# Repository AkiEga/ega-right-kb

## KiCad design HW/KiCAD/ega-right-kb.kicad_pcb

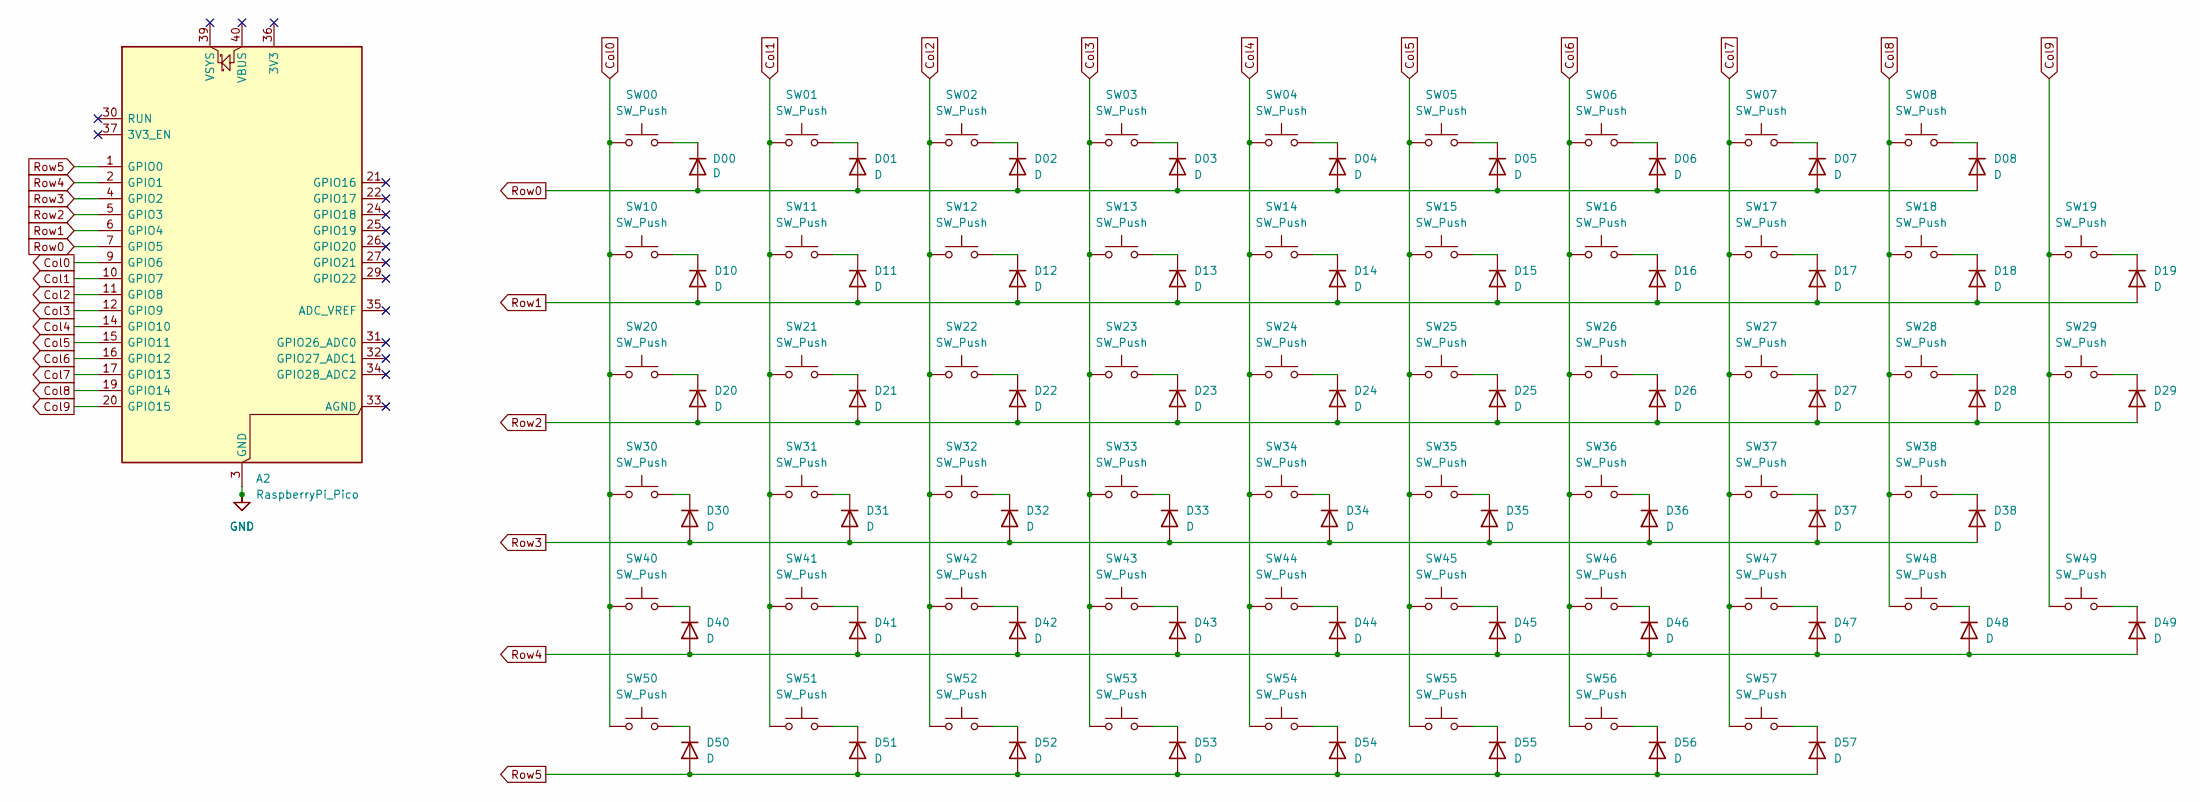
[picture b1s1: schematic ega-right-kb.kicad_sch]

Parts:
A2: RaspberryPi_Pico; RaspberryPi_Pico_Common_THT
D00, D01, D02, D03, D04, D05, D06, D07, D08, D10, D11, D12, D13, D14, D15, D16, D17, D18, D19, D20, D21, D22, D23, D24, D25, D26, D27, D28, D29, D30, D31, D32, D33, D34, D35, D36, D37, D38, D40, D41, D42, D43, D44, D45, D46, D47, D48, D49, D50, D51, D52, D53, D54, D55, D56, D57: D; D_SOD-123
SW00, SW01, SW02, SW03, SW04, SW05, SW06, SW07, SW08, SW10, SW11, SW12, SW13, SW14, SW15, SW16, SW17, SW18, SW19, SW20, SW21, SW22, SW23, SW24, SW25, SW26, SW27, SW28, SW29, SW30, SW31, SW32, SW33, SW34, SW35, SW36, SW37, SW38, SW40, SW41, SW42, SW43, SW44, SW45, SW46, SW47, SW48, SW49, SW50, SW51, SW52, SW53, SW54, SW55, SW56, SW57: SW_Push; SW_Hotswap_Kailh_MX_1.00u

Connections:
Col0: A2.9 (GPIO6), SW00.1, SW10.1, SW20.1, SW30.1, SW40.1, SW50.1
Col1: A2.10 (GPIO7), SW01.1, SW11.1, SW21.1, SW31.1, SW41.1, SW51.1
Col2: A2.11 (GPIO8), SW02.1, SW12.1, SW22.1, SW32.1, SW42.1, SW52.1
Col3: A2.12 (GPIO9), SW03.1, SW13.1, SW23.1, SW33.1, SW43.1, SW53.1
Col4: A2.14 (GPIO10), SW04.1, SW14.1, SW24.1, SW34.1, SW44.1, SW54.1
Col5: A2.15 (GPIO11), SW05.1, SW15.1, SW25.1, SW35.1, SW45.1, SW55.1
Col6: A2.16 (GPIO12), SW06.1, SW16.1, SW26.1, SW36.1, SW46.1, SW56.1
Col7: A2.17 (GPIO13), SW07.1, SW17.1, SW27.1, SW37.1, SW47.1, SW57.1
Col8: A2.19 (GPIO14), SW08.1, SW18.1, SW28.1, SW38.1, SW48.1
Col9: A2.20 (GPIO15), SW19.1, SW29.1, SW49.1
GND: A2.3 (GND), A2.8 (GND), A2.13 (GND), A2.18 (GND), A2.23 (GND), A2.28 (GND), A2.38 (GND)
unnamed: D00.1 (K), SW00.2
unnamed: D01.1 (K), SW01.2
unnamed: D02.1 (K), SW02.2
unnamed: D03.1 (K), SW03.2
unnamed: D04.1 (K), SW04.2
unnamed: D05.1 (K), SW05.2
unnamed: D06.1 (K), SW06.2
unnamed: D07.1 (K), SW07.2
unnamed: D08.1 (K), SW08.2
unnamed: D10.1 (K), SW10.2
unnamed: D11.1 (K), SW11.2
unnamed: D12.1 (K), SW12.2
unnamed: D13.1 (K), SW13.2
unnamed: D14.1 (K), SW14.2
unnamed: D15.1 (K), SW15.2
unnamed: D16.1 (K), SW16.2
unnamed: D17.1 (K), SW17.2
unnamed: D18.1 (K), SW18.2
unnamed: D19.1 (K), SW19.2
unnamed: D20.1 (K), SW20.2
unnamed: D21.1 (K), SW21.2
unnamed: D22.1 (K), SW22.2
unnamed: D23.1 (K), SW23.2
unnamed: D24.1 (K), SW24.2
unnamed: D25.1 (K), SW25.2
unnamed: D26.1 (K), SW26.2
unnamed: D27.1 (K), SW27.2
unnamed: D28.1 (K), SW28.2
unnamed: D29.1 (K), SW29.2
unnamed: D30.1 (K), SW30.2
unnamed: D31.1 (K), SW31.2
unnamed: D32.1 (K), SW32.2
unnamed: D33.1 (K), SW33.2
unnamed: D34.1 (K), SW34.2
unnamed: D35.1 (K), SW35.2
unnamed: D36.1 (K), SW36.2
unnamed: D37.1 (K), SW37.2
unnamed: D38.1 (K), SW38.2
unnamed: D40.1 (K), SW40.2
unnamed: D41.1 (K), SW41.2
unnamed: D42.1 (K), SW42.2
unnamed: D43.1 (K), SW43.2
unnamed: D44.1 (K), SW44.2
unnamed: D45.1 (K), SW45.2
unnamed: D46.1 (K), SW46.2
unnamed: D47.1 (K), SW47.2
unnamed: D48.1 (K), SW48.2
unnamed: D49.1 (K), SW49.2
unnamed: D50.1 (K), SW50.2
unnamed: D51.1 (K), SW51.2
unnamed: D52.1 (K), SW52.2
unnamed: D53.1 (K), SW53.2
unnamed: D54.1 (K), SW54.2
unnamed: D55.1 (K), SW55.2
unnamed: D56.1 (K), SW56.2
unnamed: D57.1 (K), SW57.2
Row0: A2.7 (GPIO5), D00.2 (A), D01.2 (A), D02.2 (A), D03.2 (A), D04.2 (A), D05.2 (A), D06.2 (A), D07.2 (A), D08.2 (A)
Row1: A2.6 (GPIO4), D10.2 (A), D11.2 (A), D12.2 (A), D13.2 (A), D14.2 (A), D15.2 (A), D16.2 (A), D17.2 (A), D18.2 (A), D19.2 (A)
Row2: A2.5 (GPIO3), D20.2 (A), D21.2 (A), D22.2 (A), D23.2 (A), D24.2 (A), D25.2 (A), D26.2 (A), D27.2 (A), D28.2 (A), D29.2 (A)
Row3: A2.4 (GPIO2), D30.2 (A), D31.2 (A), D32.2 (A), D33.2 (A), D34.2 (A), D35.2 (A), D36.2 (A), D37.2 (A), D38.2 (A)
Row4: A2.2 (GPIO1), D40.2 (A), D41.2 (A), D42.2 (A), D43.2 (A), D44.2 (A), D45.2 (A), D46.2 (A), D47.2 (A), D48.2 (A), D49.2 (A)
Row5: A2.1 (GPIO0), D50.2 (A), D51.2 (A), D52.2 (A), D53.2 (A), D54.2 (A), D55.2 (A), D56.2 (A), D57.2 (A)

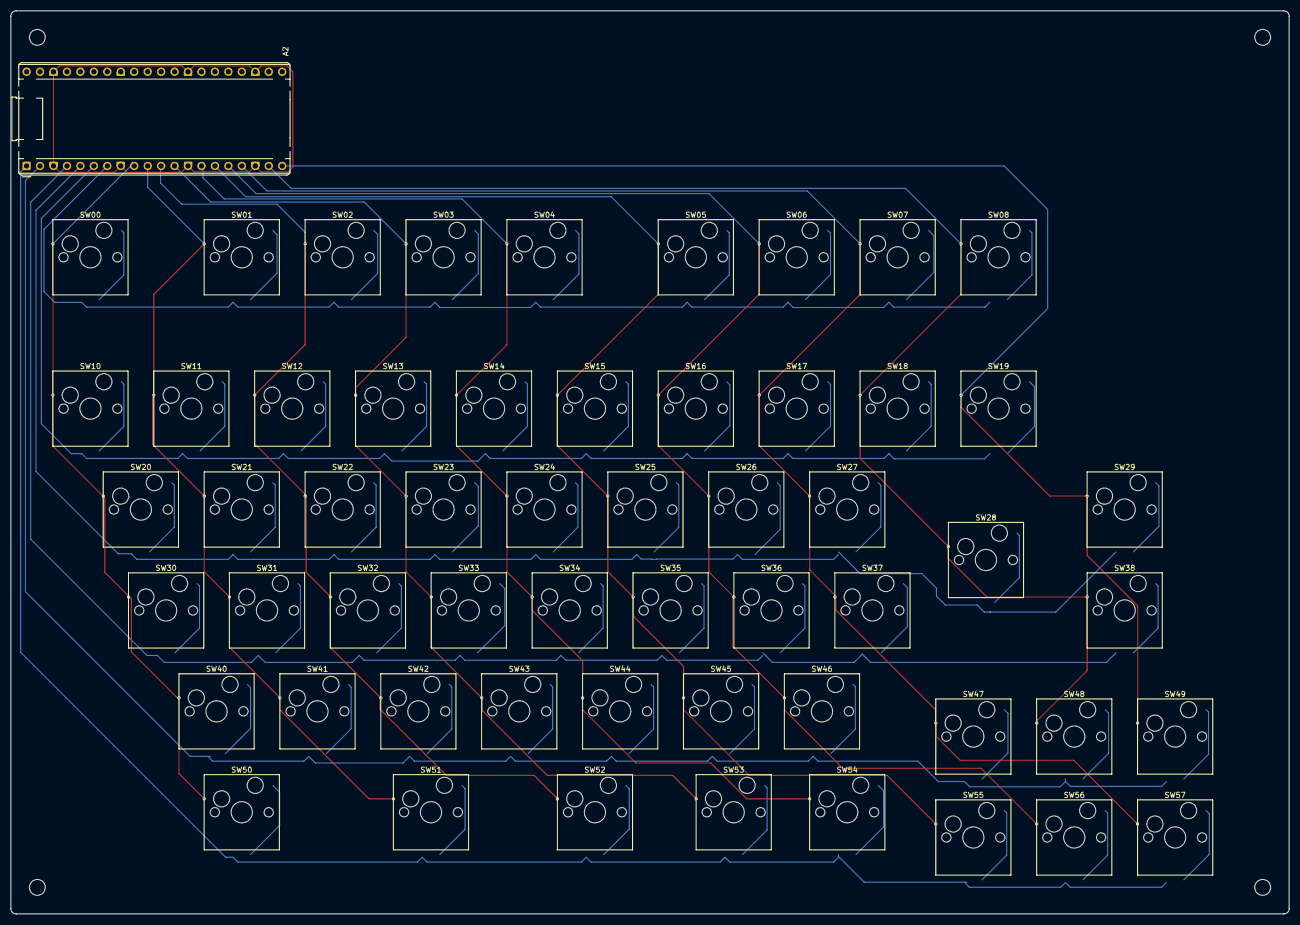
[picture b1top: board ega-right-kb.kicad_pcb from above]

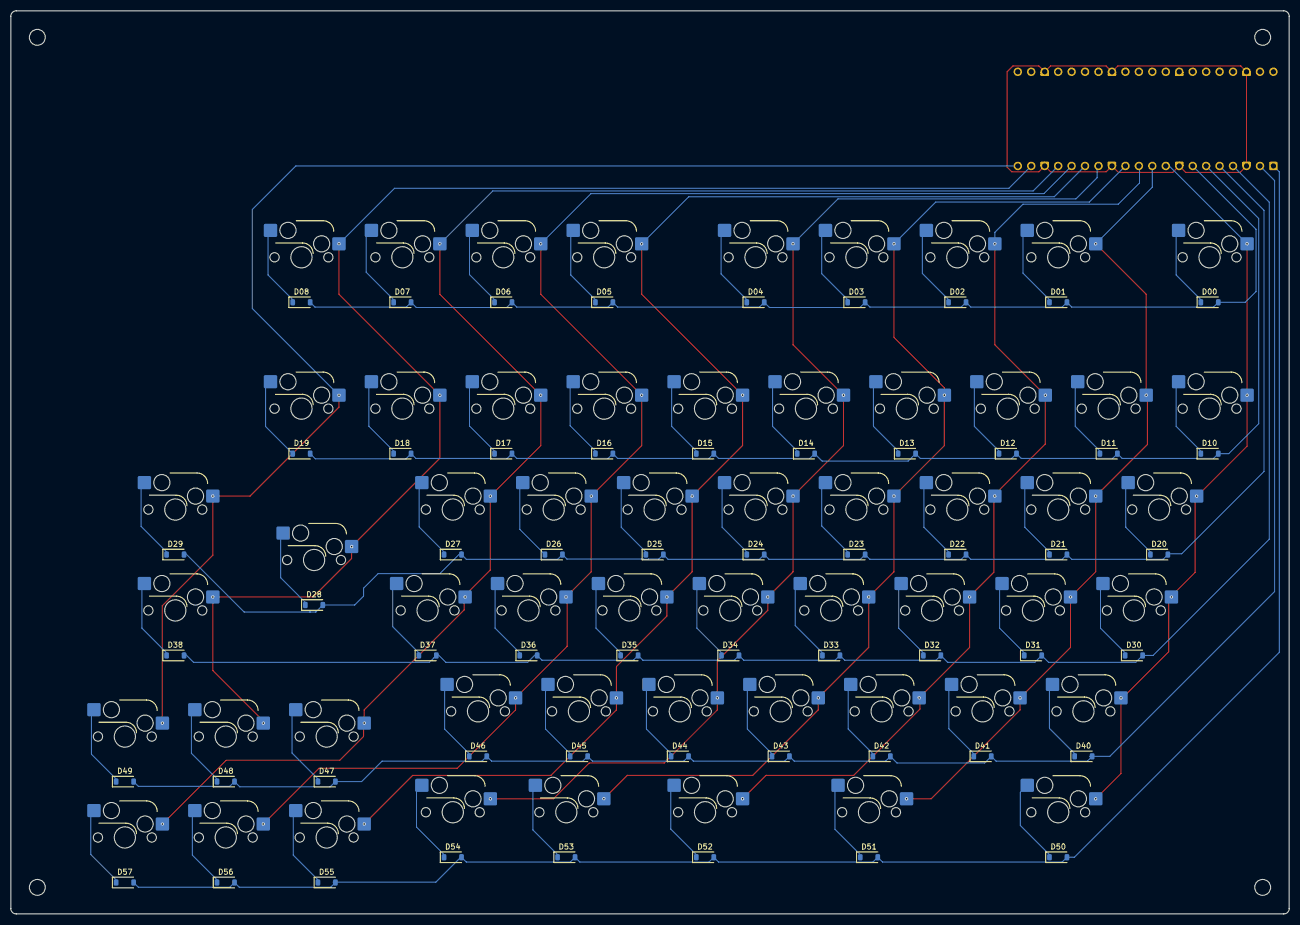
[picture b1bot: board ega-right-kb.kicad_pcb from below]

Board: 2 copper layers, 241.3 x 170.5 mm, 113 parts (56 on the bottom side), 73 nets.

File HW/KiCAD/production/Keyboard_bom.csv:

Designator,Footprint,Quantity,Value,LCSC Part #
A2,RaspberryPi_Pico_Common_THT,1,RaspberryPi_Pico,
"D00, D01, D02, D03, D04, D05, D06, D07, D08, D10, D11, D12, D13, D14, D15, D16, D17, D18, D19, D20, D21, D22, D23, D24, D25, D26, D27, D28, D29, D30, D31, D32, D33, D34, D35, D36, D37, D38, D40, D41, D42, D43, D44, D45, D46, D47, D48, D49, D50, D51, D52, D53, D54, D55, D56, D57",D_SOD-123,56,D,
"SW00, SW01, SW02, SW03, SW04, SW05, SW06, SW07, SW08, SW10, SW11, SW12, SW13, SW14, SW15, SW16, SW17, SW18, SW19, SW20, SW21, SW22, SW23, SW24, SW25, SW26, SW27, SW28, SW29, SW30, SW31, SW32, SW33, SW34, SW35, SW36, SW37, SW38, SW40, SW41, SW42, SW43, SW44, SW45, SW46, SW47, SW48, SW49, SW50, SW51, SW52, SW53, SW54, SW55, SW56, SW57",SW_Hotswap_Kailh_MX_1.00u,56,SW_Push,

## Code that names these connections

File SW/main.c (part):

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#define NUM_KEYS 50

// GPIO pin for keyboard as matrix circuit (from KiCAD netlist)
#define GPIO_ROW_0 (5)   // Row0 = GPIO5
#define GPIO_ROW_1 (4)   // Row1 = GPIO4
#define GPIO_ROW_2 (3)   // Row2 = GPIO3
#define GPIO_ROW_3 (2)   // Row3 = GPIO2
#define GPIO_ROW_4 (1)   // Row4 = GPIO1
#define GPIO_ROW_5 (0)   // Row5 = GPIO0

#define GPIO_COL_0 (6)   // Col0 = GPIO6
#define GPIO_COL_1 (7)   // Col1 = GPIO7
#define GPIO_COL_2 (8)   // Col2 = GPIO8
#define GPIO_COL_3 (9)   // Col3 = GPIO9
#define GPIO_COL_4 (10)  // Col4 = GPIO10
#define GPIO_COL_5 (11)  // Col5 = GPIO11
#define GPIO_COL_6 (12)  // Col6 = GPIO12
#define GPIO_COL_7 (13)  // Col7 = GPIO13
#define GPIO_COL_8 (14)  // Col8 = GPIO14
#define GPIO_COL_9 (15)  // Col9 = GPIO15

// Row and Column GPIO arrays
static const uint row_pins[NUM_ROWS] = {
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
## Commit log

2025-10-12 first commit. Files in the SW folder was imported pico_arcade_controller.
2025-10-12 add a workspace file
2025-10-12 modified CMakeLists.txt to rename as ega-right-kb
2025-11-29 feat: add initial configuration for keyboard GPIO mapping and HID report handling
2025-11-30 feat: renewed from example project of pico sdk of hid component
2025-11-30 fix: update .gitignore and workspace configuration for build paths
2025-11-30 fix: update includePath in c_cpp_properties.json for toolchain configuration
2025-11-30 refactor: remove unused led_blinking_task and related code
2025-11-30 feat: add GPIO initialization for keyboard matrix in main.c
2025-11-30 refactor: remove unused blink_interval_ms variable from main.c
2025-11-30 refactor: update executable name and replace button read logic with keyboard switch read function
2025-12-08 feat: add copilot instructions for building and flashing the keyboard firmware
2025-12-08 feat: remove positions.csv and update README for ega-right-kb firmware
    - Deleted the positions.csv file as it is no longer needed.
    - Updated README.md to provide detailed information about the ega-right-kb firmware, including hardware configuration, architecture, build system, development instructions, implementation status, and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
2025-12-08 feat: add positions CSV for component placement in KiCAD production
2025-12-08 feat: add initial workspace configuration for ega-right-kb project
2025-12-08 feat: enhance keyboard state management with modifier support and matrix scanning
2025-12-13 docs: update README for improved clarity and formatting
2025-12-13 feat: refactor keyboard state management and enhance matrix scanning logic
2025-12-14 feat: update keycode mapping for JIS layout with Kanji support
2025-12-14 feat: update keycode mapping for ROW3 to include JIS "む" key support
2025-12-14 feat: update keycode mapping for ROW3, ROW4, and ROW5 to improve JIS layout support
2025-12-14 feat: add SVG generation script for keyboard plate from JSON layout
2025-12-14 chore: update code structure for better maintainability
2025-12-14 fix(svg): update document name and adjust positioning attributes in ega-right-kb-positioning-plate.svg
2025-12-14 fix(svg): change display style of path in ega-right-kb-positioning-plate.svg to none
2025-12-14 fix(svg): adjust dimensions and stroke width of the right keyboard positioning plate
2025-12-16 fix: update key mappings for ROW5 in keycode_map and README
2025-12-22 fix: update key mapping for ROW1 to include HID_KEY_KANJI3
2025-12-22 fix: update keycode mapping to support multiple layers and FN key functionality
2025-12-23 fix: update FN key handling in keycode mapping and LED behavior
2026-01-10 feat: add keyboard layout editor shortcut URL
2026-01-10 feat:レイアウト修正。十字キーなどを追加
2026-01-10 feat: 回路図修正
2026-01-13 chore: 不要なレイアウトファイルを削除
2026-01-13 chore: update code structure for improved readability and maintainability
2026-01-21 feat: add KLE to KiCAD plugin with core functionality and GUI
    - Implemented KLE to KiCAD plugin that imports keyboard layouts from keyboard-layout-editor.com JSON files.
    - Added core logic for parsing KLE JSON and placing switch and diode footprints.
    - Created GUI for user configuration and settings management.
    - Introduced cache manager for storing last used settings and execution history.
    - Added command line interface for batch processing and testing.
    - Included metadata for plugin registration in KiCAD.
2026-01-21 chore: remove unused kle2kicad.py script and add __pycache__ to .gitignore
2026-01-21 chore: メイン基板 の配線まで完成
2026-01-21 chore: update .gitignore to include additional backup directory
2026-01-21 chore: update project configuration and dependencies
2026-01-24 feat: add top plate generator for KLE to KiCAD conversion
    - Implemented TopPlateGenerator class to create switch cutouts, PCB outlines, and screw holes.
    - Added methods for generating rectangular cutouts, rounded rectangles, and screw holes.
    - Included functionality for calculating bounding boxes and generating V-cut lines.
    - Introduced support for various switch types and customizable settings.
2026-01-24 feat: update KiCAD project files and add production resources
    - Changed active layer from 0 to 25 and updated zone display mode from 0 to 1 in `ega-right-kb.kicad_prl`.
    - Added new binary file `Keyboard.zip` to the production directory.
    - Created new BOM file `Keyboard_bom.csv` with component details.
    - Added designators for components in `Keyboard_designators.csv`.
    - Included positions for components in `Keyboard_positions.csv`.
    - Updated netlist in `netlist.ipc` with new VIA specifications.
2026-02-10 feat: update GPIO pin mappings and simplify key layer handling
    - Updated GPIO pin definitions for keyboard matrix based on KiCAD netlist.
    - Reduced the number of layers from 2 to 1, simplifying the key mapping.
    - Modified key mappings for better functionality, including changes to specific keys.
    - Adjusted LED behavior to indicate any key press instead of just FN key.
2026-02-10 feat: add debugging LED functionality for key press detection
2026-02-10 feat: add SVG top plate design and update plate generation logic
2026-02-10 chore: disable LEDs blinking

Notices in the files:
SW/main.c:
The MIT License (MIT)
Copyright (c) 2019 Ha Thach (tinyusb.org)
